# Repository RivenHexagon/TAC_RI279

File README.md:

# Total Audio Concepts (TAC) Scorpion Mixing Console Overhaul
## PCB RI279

Redesign of the Bus Connector Card (PCB RI279) in order to populate it
with gold plated Audio Jacks. I made 8 of them fit a copper plated Eurocard
(100 mm x 80 mm) substrate for DIY etching.

## Made With

I named the new version RI279C and made them with KiCad 5.1.7. using a git
submodule that handles any special footprints:

https://github.com/RivenHexagon/TAC_KiCad_lib.git

## Further Modifications

The XLR Bus Out connectors were panel mounted and solder wired to the PCB as
well as the Tape Return wiring harness. I've provided two 3-pin Molex connectors
and a 2-pole pin header (GND and signal) for the wire ging out to the vu-meter.

Mirrored image of the original PCB:

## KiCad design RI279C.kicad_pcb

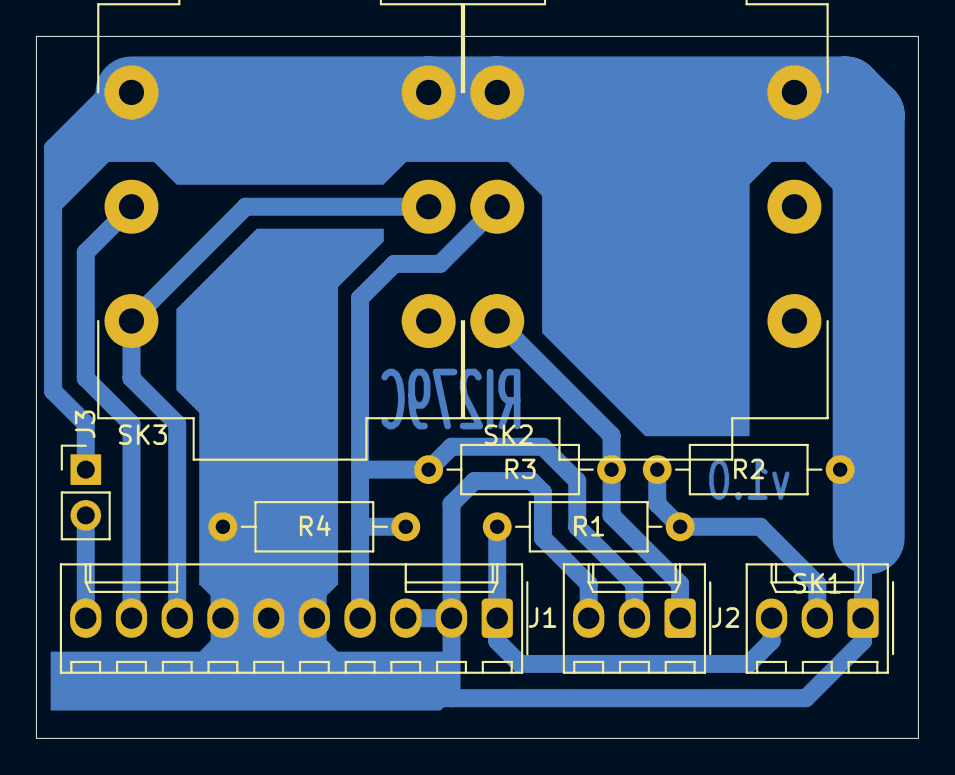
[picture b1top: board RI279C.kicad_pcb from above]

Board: 2 copper layers, 49.0 x 39.0 mm, 10 parts (0 on the bottom side), 8 nets.

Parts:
J1: Ribbon Cable; Molex_KK-254_AE-6410-10A_1x10_P2.54mm_Vertical
J2: Multiway; Molex_KK-254_AE-6410-03A_1x03_P2.54mm_Vertical
J3: Meter; PinHeader_1x02_P2.54mm_Vertical
R1: 3k; R_Axial_DIN0207_L6.3mm_D2.5mm_P10.16mm_Horizontal
R2: 1k; R_Axial_DIN0207_L6.3mm_D2.5mm_P10.16mm_Horizontal
R3: 62k; R_Axial_DIN0207_L6.3mm_D2.5mm_P10.16mm_Horizontal
R4: 22k; R_Axial_DIN0207_L6.3mm_D2.5mm_P10.16mm_Horizontal
SK1: Buss Out; Molex_KK-254_AE-6410-03A_1x03_P2.54mm_Vertical
SK2: Tape/FX; CL13345
SK3: Insert; CL13345

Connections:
GND: J1.2, J1.3, J1.5, J1.6, J1.7, J2.3, J3.1, R2.1, R4.2, SK1.1, SK2.S, SK2.SN, SK3.S, SK3.SN
unnamed: J1.1, R1.2, SK1.3
unnamed: J1.4, J2.2, R3.1, R4.1, SK2.R
unnamed: J1.8, SK3.RN, SK3.T
unnamed: J1.9, SK3.R
unnamed: J1.10, J3.2
unnamed: J2.1, R3.2, SK2.T
unnamed: R1.1, R2.2, SK1.2

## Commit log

2020-10-26 prototype ready
2020-10-26 aligned edge cuts to mm grid, 39 mm x 49 mm
2020-10-26 updated dxf files and plot output folder
2020-11-30 added TAC library as submodule
2020-11-30 readme correction
2020-11-30 lib update
